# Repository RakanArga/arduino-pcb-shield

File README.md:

# Earthquake Emergency Beacon – Arduino Uno Shield

Created to fulfill an assignment for *Rangkaian Listrik dan Elektronika* (Electrical Circuits and Electronics). This custom Arduino Uno R3 shield connects the project's sensors and indicators through fixed headers instead of loose jumper wires. 

## Overview

The beacon watches for an earthquake or a call for help. An SW-420 module detects vibration and a MAX4466 microphone module picks up loud sound. When either one triggers, the Arduino sounds a buzzer and flashes a red LED so people nearby can locate the device.

## Features
a. Vibration Detection (SW-420, Digital Output)
b. Sound Detection (MAX4466 Microphone Module, Analog Output)
c. Audible Alarm (Buzzer Module) and Visual Indicator (Red Led)
d. Plugs straight onto an Arduino Uno R3 (official 2700 × 2100 mil outline and header positions)

## Hardware
| Part | Qty | Notes |
|---|---|---|
| Arduino Uno R3 | 1 | Powered over USB |
| SW-420 vibration sensor module | 1 | Digital output (DO) |
| MAX4466 microphone amplifier module | 1 | Analog output (OUT) |
| Buzzer module, 3-pin | 1 | VCC / I/O / GND |
| Red LED, 5 mm | 1 | D1 |
| Resistor 220 Ω, 1/4 W | 1 | R1, LED current limiting |
| Pin headers | – | Uno R3 headers and the sensor connectors |

## Wiring

All signals go to the Uno through the shield headers. VCC is the Uno's 5V pin.

| Part | Connector | Pin on module | Uno pin |
|---|---|---|---|
| Buzzer | J5 | I/O | D8 |
| SW-420 vibration sensor | J7 | DO | D9 |
| MAX4466 microphone | J6 | OUT | A0 |
| Red LED (D1) via R1 | – | anode side of R1 | D10 |

Power: every module takes VCC from the Uno's 5V pin and GND from the Uno's GND pins (shared GND zone on the back layer).

### Connector pinouts

| Connector | Pin 1 | Pin 2 | Pin 3 |
|---|---|---|---|
| J5 Buzzer | VCC | I/O (D13) | GND |
| J7 SW-420 | DO (D10) | GND | VCC |
| J6 MAX4466 | OUT (A0) | GND | VCC |
| LED| D9 | GND |

Check these orders against the printed labels on your own modules, because the pin order differs between manufacturers.

## References & Images

LINK: https://aihg.drugros-spb.org/arduino-uno-schematic-dimension-carte-arduino-uno/

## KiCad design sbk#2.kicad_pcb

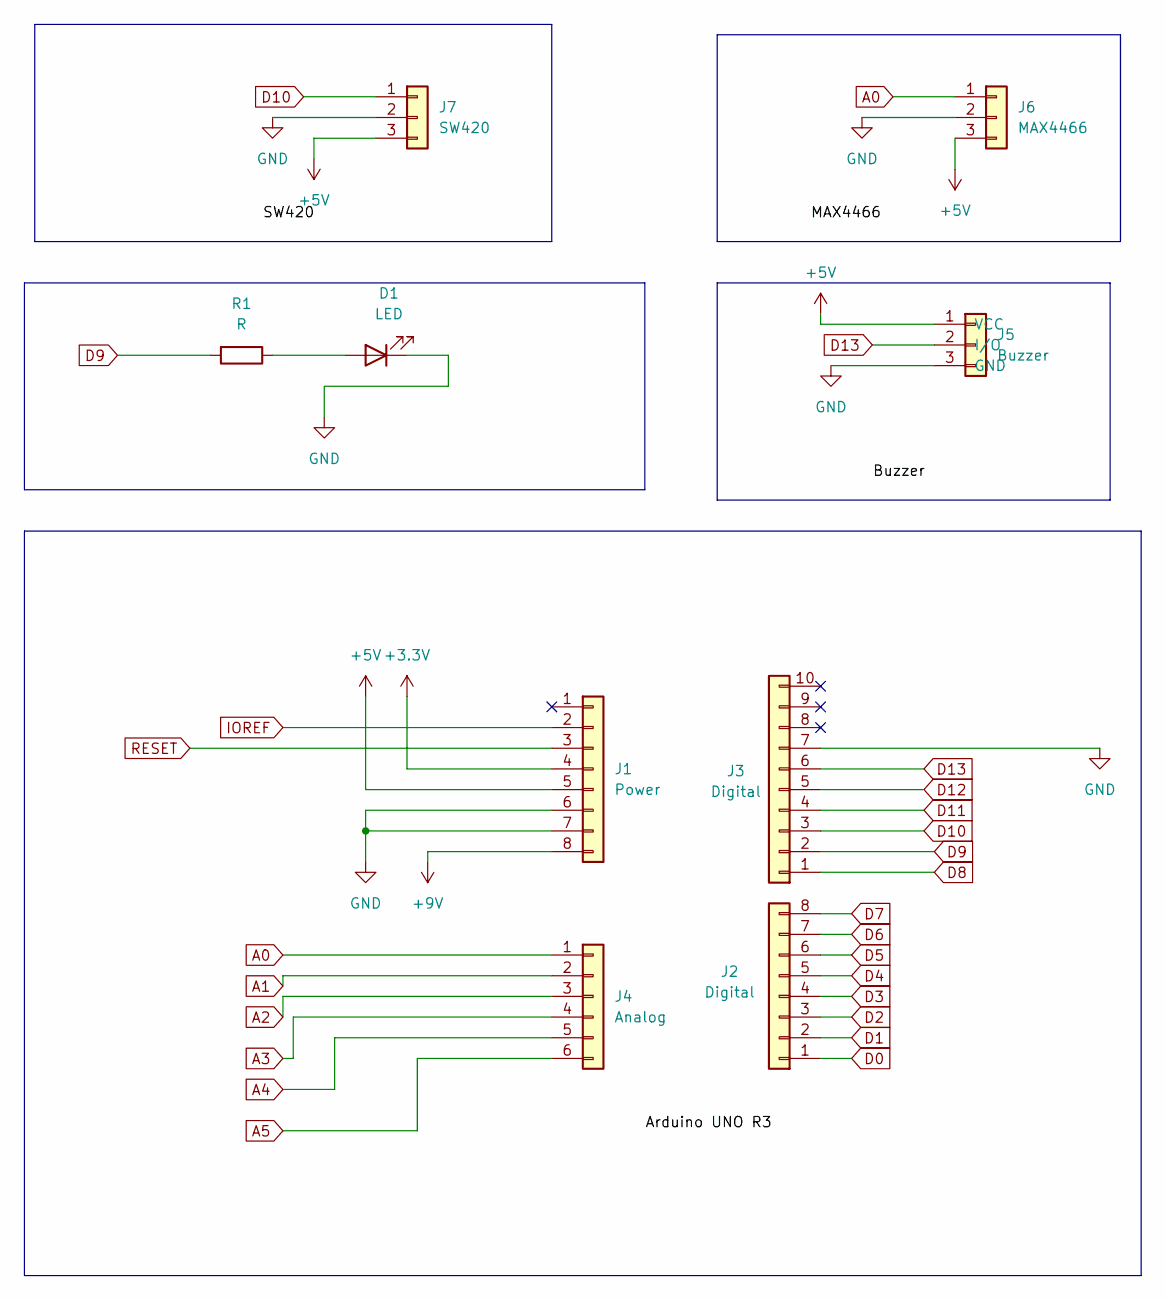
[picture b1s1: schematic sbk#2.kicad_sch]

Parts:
D1: LED; LED_D5.0mm
J1: Power; PinHeader_1x08_P2.54mm_Vertical
J2: Digital; PinHeader_1x08_P2.54mm_Vertical
J3: Digital; PinHeader_1x10_P2.54mm_Vertical
J4: Analog; PinHeader_1x06_P2.54mm_Vertical
J5: Buzzer; PinSocket_1x03_P2.54mm_Vertical
J6: MAX4466; PinSocket_1x03_P2.54mm_Vertical
J7: SW420; PinSocket_1x03_P2.54mm_Vertical
R1: R; R_Axial_DIN0411_L9.9mm_D3.6mm_P12.70mm_Horizontal

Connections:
+3.3V: J1.4
+5V: J1.5, J5.1 (VCC), J6.3, J7.3
+9V: J1.8
A0: J4.1, J6.1
A1: J4.2
A2: J4.3
A3: J4.4
A4: J4.5
A5: J4.6
D0: J2.1
D1: J2.2
D2: J2.3
D3: J2.4
D4: J2.5
D5: J2.6
D6: J2.7
D7: J2.8
D8: J3.1
D9: J3.2, R1.2
D10: J3.3, J7.1
D11: J3.4
D12: J3.5
D13: J3.6, J5.2 (I/O)
GND: D1.1 (K), J1.6, J1.7, J3.7, J5.3 (GND), J6.2, J7.2
IOREF: J1.2
unnamed: D1.2 (A), R1.1
RESET: J1.3

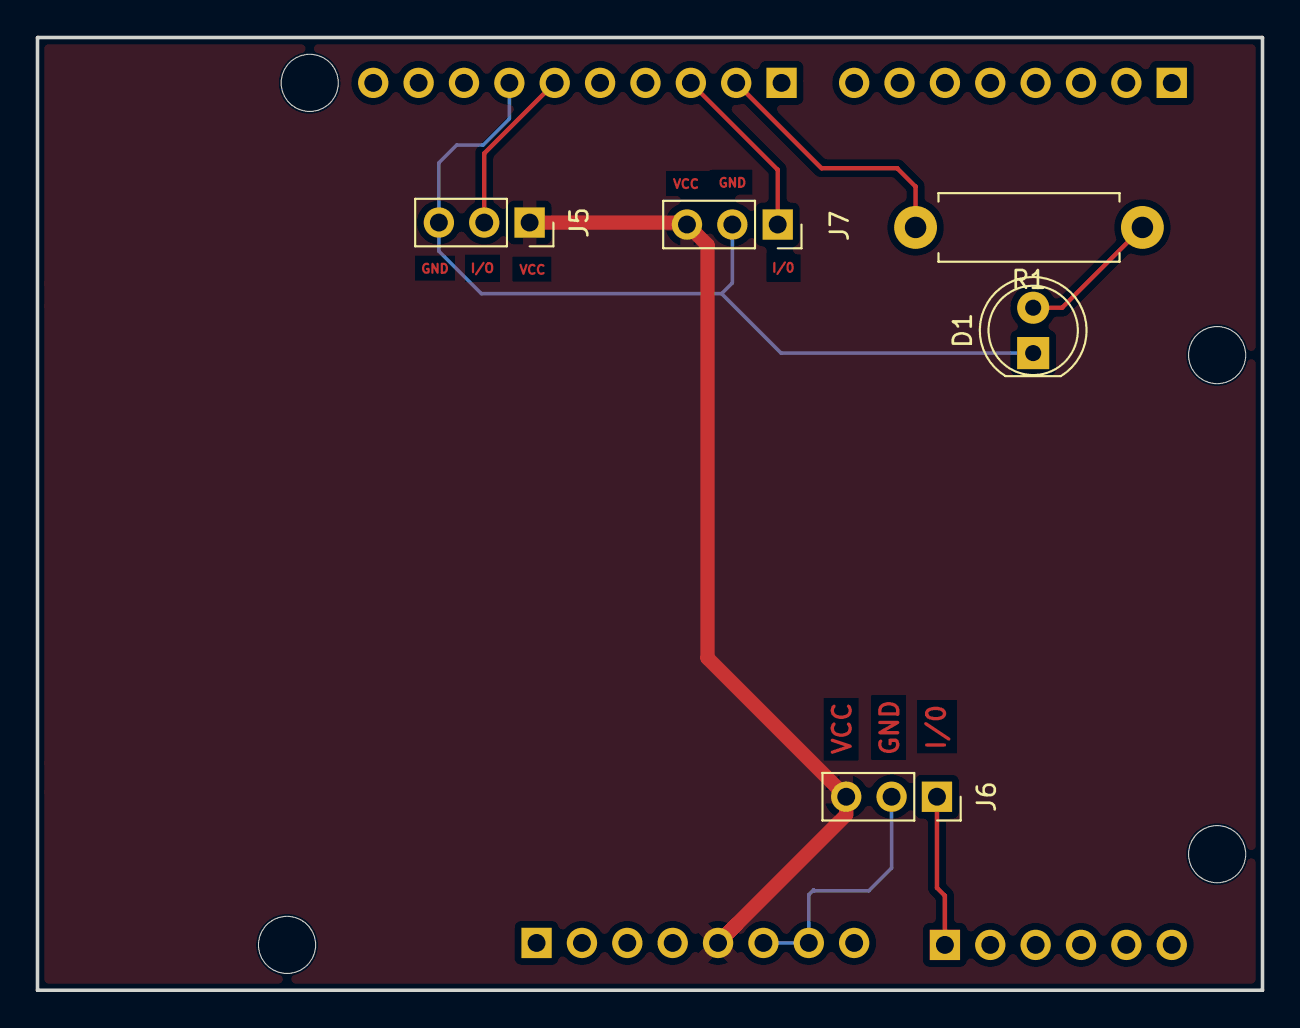
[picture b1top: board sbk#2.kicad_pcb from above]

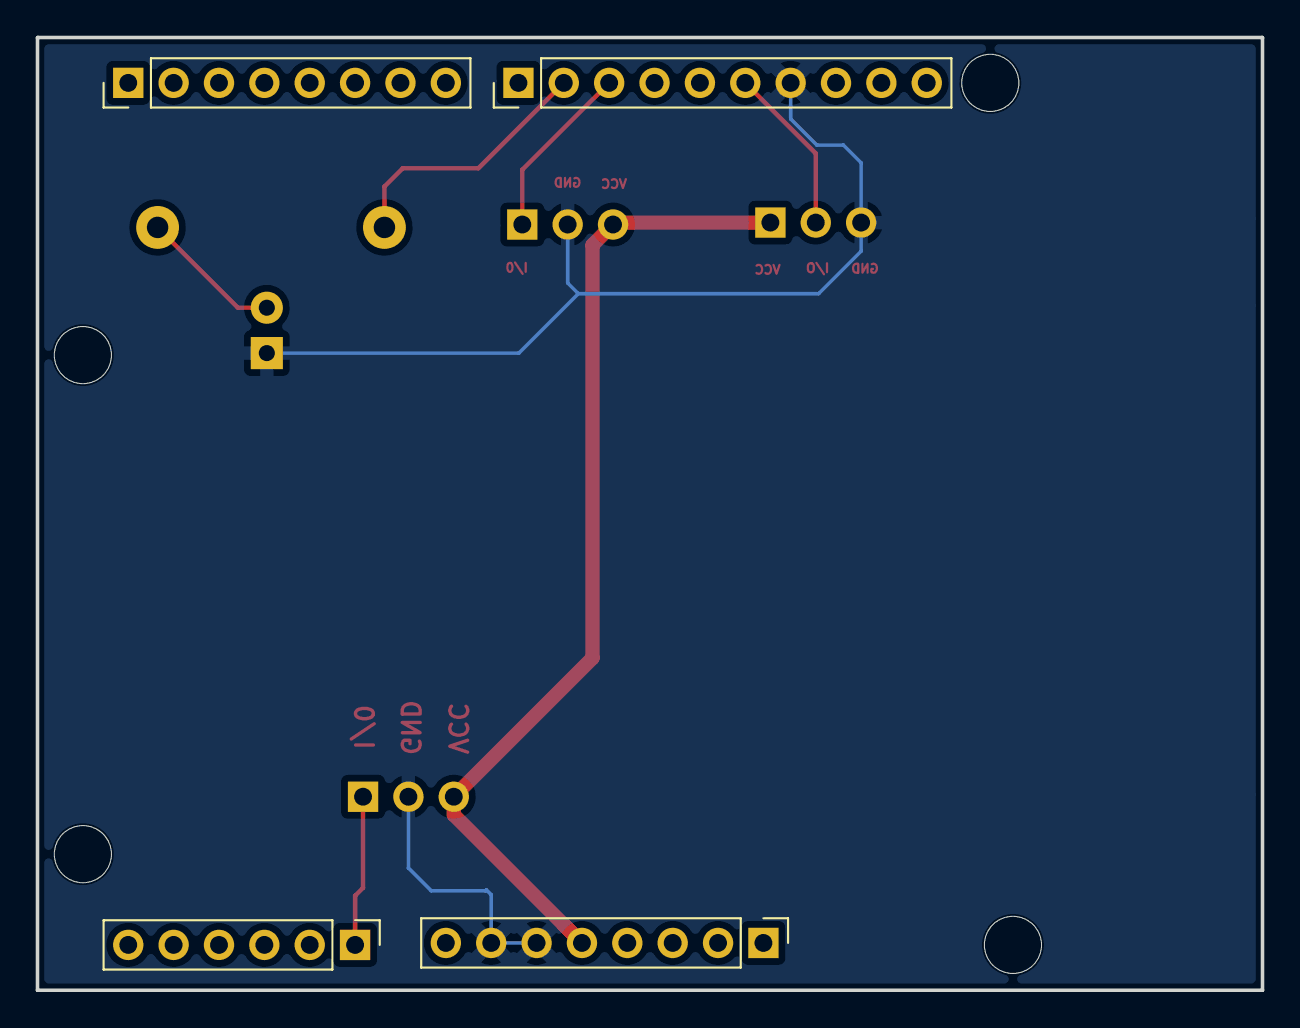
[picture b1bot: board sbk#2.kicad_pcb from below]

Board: 2 copper layers, 68.6 x 53.3 mm, 9 parts (4 on the bottom side), 7 nets.
